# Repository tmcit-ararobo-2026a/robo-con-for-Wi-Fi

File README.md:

# < robo-con-for-Wi-Fi >

<!-- 一行でプロジェクトを説明する -->
the code and pcb in this repository is wireless robot's controller.     

## 目次

1. [概要](#1-概要)
2. [ドキュメント](#2-ドキュメント)
3. [コントリビューション](#3-コントリビューション)
4. [ビルド・使い方](#4-ビルド使い方)
5. [システム構成](#5-システム構成)
6. [ライセンス](#6-ライセンス)

## 1. 概要

<!-- プロジェクトの目的・背景・解決する課題を記述 -->
ロボコンなどの会場のなかでは2.4GHzもしくは5GHzといった周波数帯は多くの場合かなり混雑していることが多い。    
こういった大会で無線による有利は勝敗に大きく作用するため、使用する周波数はできるだけ混雑していないことが望ましい。  
そのため、6GHzを使うコントローラーを作成する。  

## 2. ドキュメント

| ドキュメント | 説明 |
| :-: | :-: |
| [CONTRIBUTING.md](./CONTRIBUTING.md) | 開発フロー・コミット規約・コーディング規約 |
| [docs/coding-rules.md](./docs/coding-rules.md) | コーディング規約の詳細 |
| [docs/uml/](./docs/uml/) | UML図 |

## 3. コントリビューション

[CONTRIBUTING.md](./CONTRIBUTING.md) を参照してください。

## 4. ビルド・使い方

<!-- ビルドのやり方 -->
<!-- 使い方 -->

## 5. システム構成

<!-- ROS2ノード構成・STM32との通信方式・ハードウェア構成 等 -->
<!-- 依存クラスが3つ以上ある場合は docs/uml/ にUML図を作成し、ここにリンクする -->

## 6. ライセンス

本リポジトリは [MITライセンス](./LICENSE) のもとで公開されています。

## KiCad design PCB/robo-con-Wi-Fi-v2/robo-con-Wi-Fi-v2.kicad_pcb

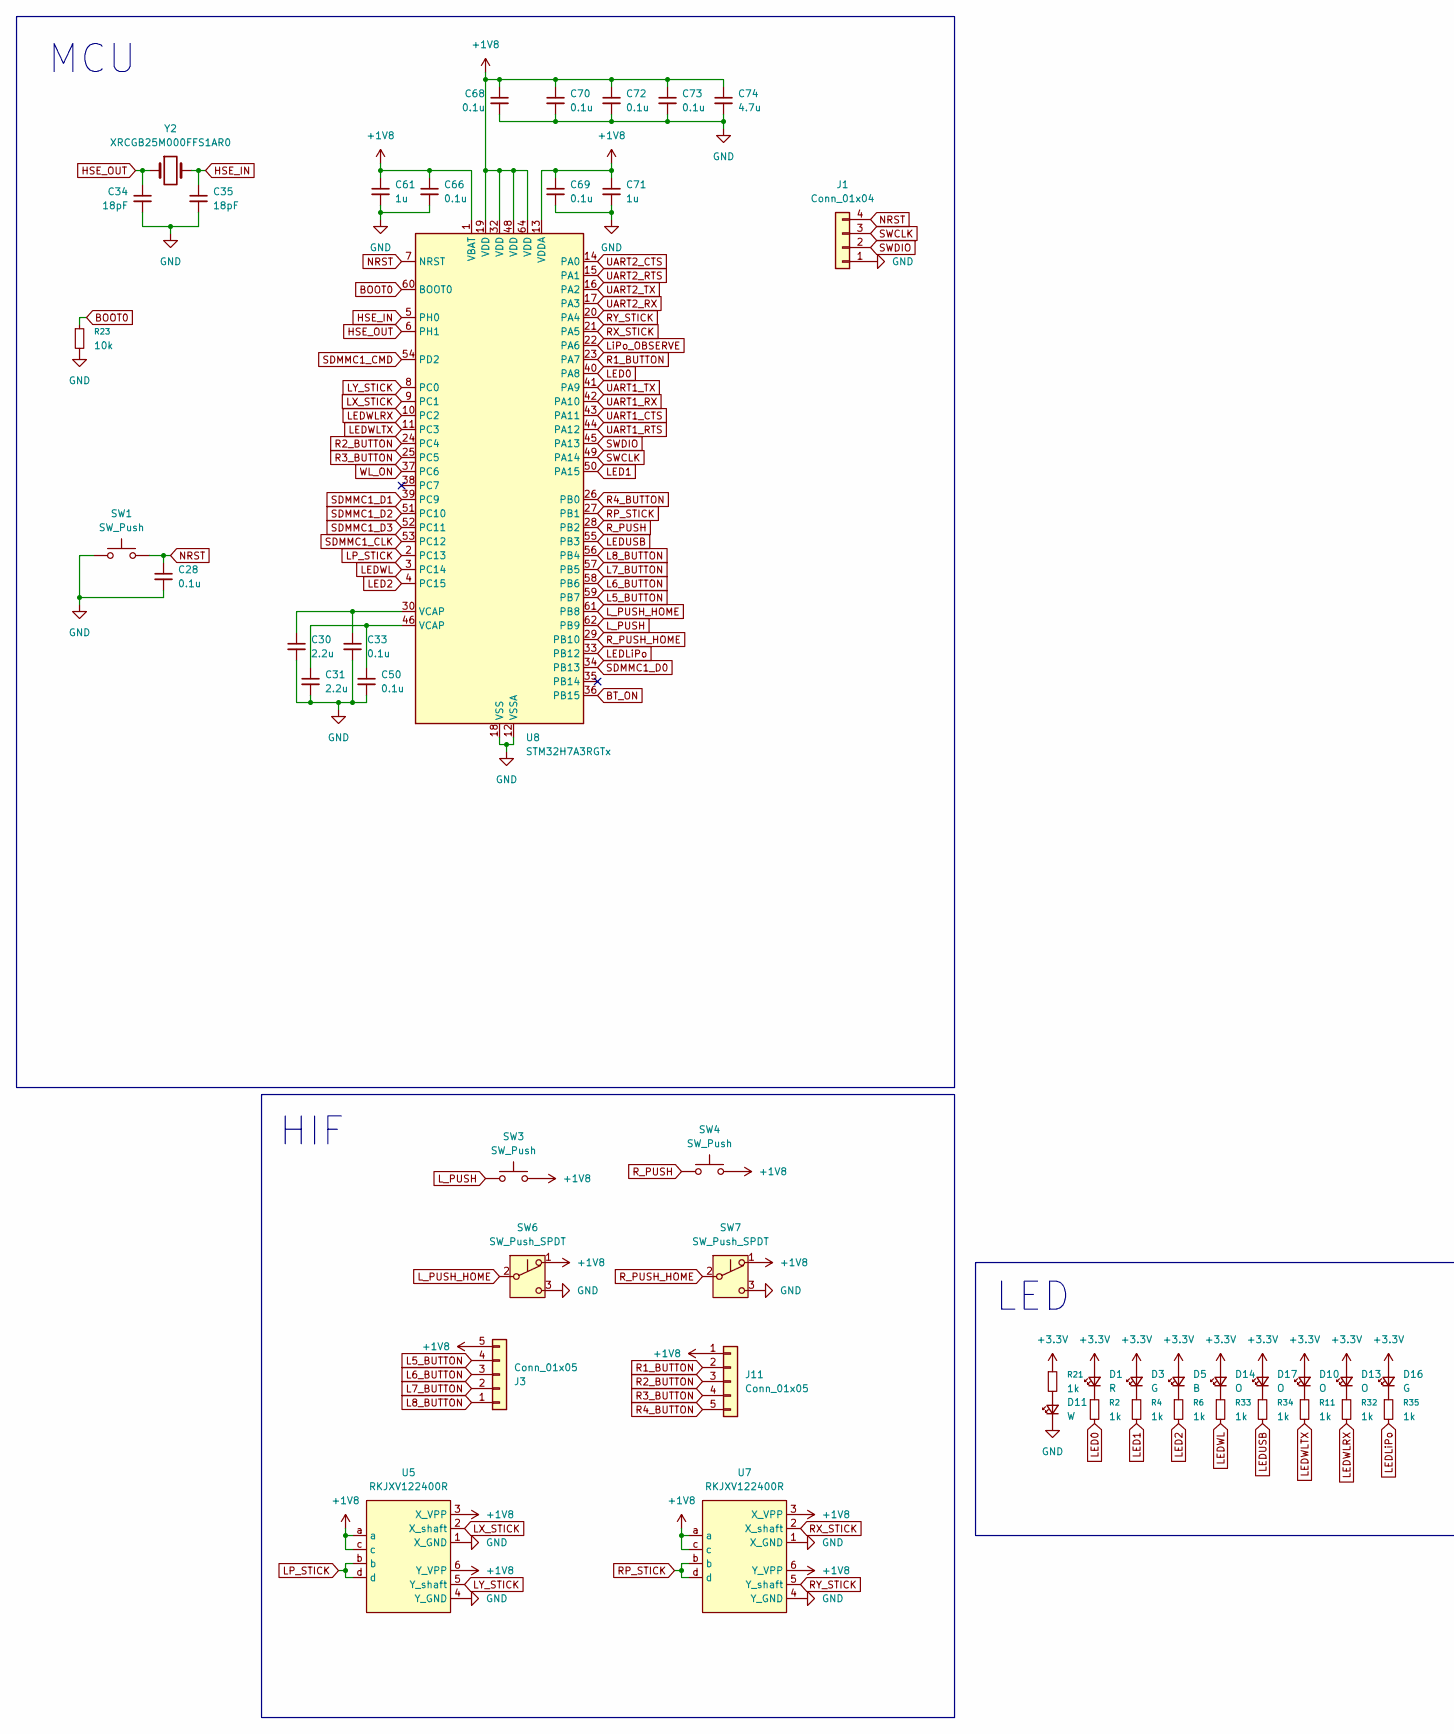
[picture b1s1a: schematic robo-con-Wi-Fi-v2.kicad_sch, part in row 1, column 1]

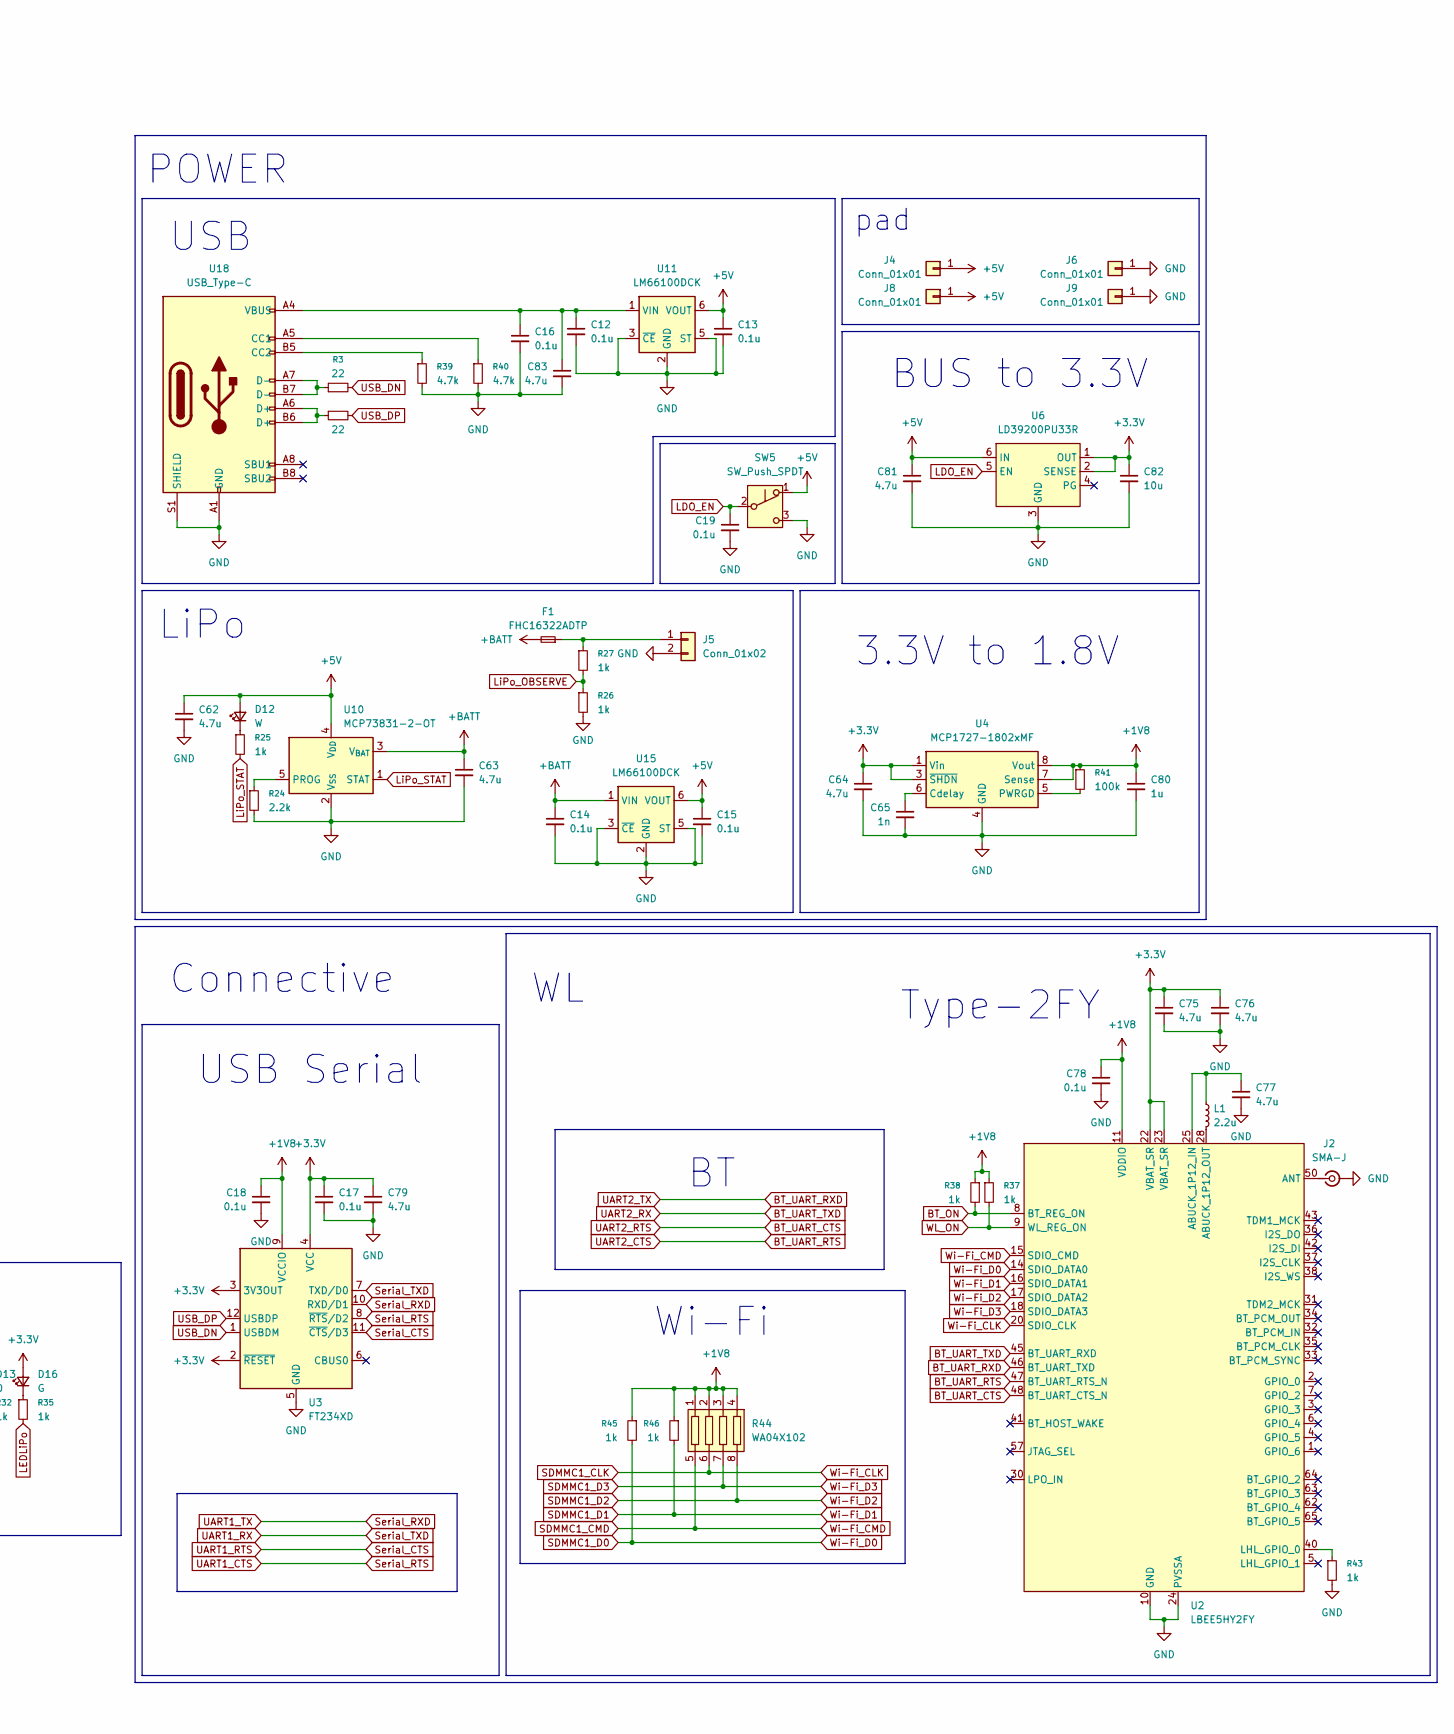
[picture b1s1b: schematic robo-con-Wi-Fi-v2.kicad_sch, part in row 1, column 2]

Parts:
C12, C13, C14, C15, C16, C17, C18, C19, C28, C33, C50, C66, C68, C69, C70, C72, C73, C78: 0.1u; C_0402_1005Metric_Pad0.74x0.62mm_HandSolder
C30, C31: 2.2u; C_0402_1005Metric_Pad0.74x0.62mm_HandSolder
C34, C35: 18pF; C_0402_1005Metric_Pad0.74x0.62mm_HandSolder
C61, C71, C80: 1u; C_0402_1005Metric_Pad0.74x0.62mm_HandSolder
C62, C63, C64, C74, C75, C76, C77, C79, C81, C83: 4.7u; C_0402_1005Metric_Pad0.74x0.62mm_HandSolder
C65: 1n; C_0402_1005Metric_Pad0.74x0.62mm_HandSolder
C82: 10u; C_0603_1608Metric_Pad1.08x0.95mm_HandSolder
D1: R; D_0603_1608Metric_Pad1.05x0.95mm_HandSolder
D3, D16: G; D_0603_1608Metric_Pad1.05x0.95mm_HandSolder
D5: B; D_0603_1608Metric_Pad1.05x0.95mm_HandSolder
D10, D13, D14, D17: O; D_0603_1608Metric_Pad1.05x0.95mm_HandSolder
D11, D12: W; D_0603_1608Metric_Pad1.05x0.95mm_HandSolder
F1: FHC16322ADTP; L_0603_1608Metric_Pad1.05x0.95mm_HandSolder
J1: Conn_01x04; PinSocket_1x04_P2.54mm_Vertical
J2: SMA-J; SMA_Conn
J3, J11: Conn_01x05; JST_ZH_B5B-ZR_1x05_P1.50mm_Vertical
J4, J6, J8, J9: Conn_01x01; SolderWirePad_1x01_SMD_1.5x3mm
J5: Conn_01x02; JST_PH_S2B-PH-K_1x02_P2.00mm_Horizontal
L1: 2.2u; L_1008_2520Metric_Pad1.43x2.20mm_HandSolder
R2, R4, R6, R11, R21, R25, R32, R33, R34, R35, R37, R38, R43, R45, R46: 1k; R_0402_1005Metric_Pad0.72x0.64mm_HandSolder
R3, R5: 22; R_0402_1005Metric_Pad0.72x0.64mm_HandSolder
R23: 10k; R_0402_1005Metric_Pad0.72x0.64mm_HandSolder
R24: 2.2k; R_0603_1608Metric_Pad0.98x0.95mm_HandSolder
R26, R27: 1k; R_0603_1608Metric_Pad0.98x0.95mm_HandSolder
R39, R40: 4.7k; R_0402_1005Metric_Pad0.72x0.64mm_HandSolder
R41: 100k; R_0603_1608Metric_Pad0.98x0.95mm_HandSolder
R44: WA04X102
SW1: SW_Push; switch_TVAF06-A020B-R
SW3, SW4: SW_Push; SKHHLPA010
SW5: SW_Push_SPDT; 4MS1R202M6QES
SW6, SW7: SW_Push_SPDT; 8MS8P1B05VS2QES-C13
U2: LBEE5HY2FY
U3: FT234XD; WDFN-12-1EP_3x3mm_P0.45mm_EP1.7x2.5mm
U4: MCP1727-1802xMF; DFN-8-1EP_3x3mm_P0.65mm_EP1.55x2.4mm
U5, U7: RKJXV122400R
U6: LD39200PU33R; DFN-6-1EP_3x3mm_P0.95mm_EP1.7x2.6mm
U8: STM32H7A3RGTx; LQFP-64_10x10mm_P0.5mm
U10: MCP73831-2-OT; SOT-23-5
U11, U15: LM66100DCK; SOT-363_SC-70-6
U18: USB_Type-C; USB_C_Receptacle_Nelton_5077CR-16-SMC2-BK-TR
Y2: XRCGB25M000FFS1AR0

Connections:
+1V8: C18.1, C61.1, C66.1, C68.1, C69.1, C70.1, C71.1, C72.1, C73.1, C74.1, C78.1, C80.1, J3.5, J11.1, R37.1, R38.1, R41.1, R44.1, R44.2, R44.3, R44.4, R45.1, R46.1, SW3.2, SW4.2, SW6.1 (A), SW7.1 (A), U2.11 (VDDIO), U3.9 (VCCIO), U4.7 (Sense), U4.8 (Vout), U5.3 (X_VPP), U5.6 (Y_VPP), U5.a, U5.c, U7.3 (X_VPP), U7.6 (Y_VPP), U7.a, U7.c, U8.1 (VBAT), U8.13 (VDDA), U8.19 (VDD), U8.32 (VDD), U8.48 (VDD), U8.64 (VDD)
+3.3V: C17.1, C64.1, C75.1, C76.1, C79.1, C82.1, D1.2 (A), D3.2 (A), D5.2 (A), D10.2 (A), D13.2 (A), D14.2 (A), D16.2 (A), D17.2 (A), R21.1, U2.22 (VBAT_SR), U2.23 (VBAT_SR), U3.2 (~RESET), U3.3 (3V3OUT), U3.4 (VCC), U4.1 (Vin), U4.2 (Vin), U4.3 (~SHDN), U6.1 (OUT), U6.2 (SENSE)
+5V: C13.1, C15.1, C62.1, C81.1, D12.2 (A), J4.1 (Pin_1_1), J8.1 (Pin_1_1), SW5.1 (A), U6.6 (IN), U10.4 (V_{DD}), U11.6 (VOUT), U15.6 (VOUT)
+BATT: C14.1, C63.1, F1.2, U10.3 (V_{BAT}), U15.1 (VIN)
BOOT0: R23.1, U8.60 (BOOT0)
BT_ON: R38.2, U2.8 (BT_REG_ON), U8.36 (PB15)
BT_UART_CTS: U2.48 (BT_UART_CTS_N), U8.15 (PA1)
BT_UART_RTS: U2.47 (BT_UART_RTS_N), U8.14 (PA0)
BT_UART_RXD: U2.46 (BT_UART_TXD), U8.16 (PA2)
BT_UART_TXD: U2.45 (BT_UART_RXD), U8.17 (PA3)
GND: C12.2, C13.2, C14.2, C15.2, C16.2, C17.2, C18.2, C19.2, C28.2, C30.2, C31.2, C33.2, C34.2, C35.2, C50.2, C61.2, C62.2, C63.2, C64.2, C65.2, C66.2, C68.2, C69.2, C70.2, C71.2, C72.2, C73.2, C74.2, C75.2, C76.2, C77.2, C78.2, C79.2, C80.2, C81.2, C82.2, C83.2, D11.1 (K), J1.1, J2.2 (Ext), J5.2, J6.1 (Pin_1_1), J9.1 (Pin_1_1), R23.2, R24.2, R26.2, R39.2, R40.2, R43.2, SW1.1, SW5.3 (C), SW6.3 (C), SW7.3 (C), U2.10 (GND), U2.12 (GND), U2.13 (GND), U2.19 (GND), U2.21 (GND), U2.24 (PVSSA), U2.26 (PVSSA), U2.27 (PVSSA), U2.29 (GND), U2.39 (GND), U2.44 (GND), U2.49 (GND), U2.51 (GND), U2.52 (GND), U2.53 (GND), U2.55 (GND), U2.56 (GND), U2.58 (GND), U2.59 (GND), U2.60 (GND), U2.61 (GND), U2.66 (GND), U2.67 (GND), U2.68 (GND), U2.69 (GND), U2.70 (GND), U2.71 (GND), U2.72 (GND), U3.5 (GND), U3.13 (GND), U4.4 (GND), U4.9 (GND), U5.1 (X_GND), U5.4 (Y_GND), U6.3 (GND), U6.7 (GND), U7.1 (X_GND), U7.4 (Y_GND), U8.12 (VSSA), U8.18 (VSS), U8.31 (VSS), U8.47 (VSS), U8.63 (VSS), U10.2 (V_{SS}), U11.2 (GND), U11.3 (~CE), U11.5 (ST), U15.2 (GND), U15.3 (~CE), U15.5 (ST), U18.A1 (GND), U18.B1 (GND), U18.S1 (SHIELD)
HSE_IN: C35.1, U8.5 (PH0), Y2.3 (2)
HSE_OUT: C34.1, U8.6 (PH1), Y2.1
L5_BUTTON: J3.4, U8.59 (PB7)
L6_BUTTON: J3.3, U8.58 (PB6)
L7_BUTTON: J3.2, U8.57 (PB5)
L8_BUTTON: J3.1, U8.56 (PB4)
LDO_EN: C19.1, SW5.2 (B), U6.5 (EN)
LED0: R2.2, U8.40 (PA8)
LED1: R4.2, U8.50 (PA15)
LED2: R6.2, U8.4 (PC15)
LEDLiPo: R35.2, U8.33 (PB12)
LEDUSB: R34.2, U8.55 (PB3)
LEDWL: R33.2, U8.3 (PC14)
LEDWLRX: R32.2, U8.10 (PC2)
LEDWLTX: R11.2, U8.11 (PC3)
LP_STICK: U5.b, U5.d, U8.2 (PC13)
LX_STICK: U5.2 (X_shaft), U8.9 (PC1)
LY_STICK: U5.5 (Y_shaft), U8.8 (PC0)
L_PUSH: SW3.1, U8.62 (PB9)
L_PUSH_HOME: SW6.2 (B), U8.61 (PB8)
LiPo_OBSERVE: R26.1, R27.2, U8.22 (PA6)
LiPo_STAT: R25.2, U10.1 (STAT)
NRST: C28.1, J1.4, SW1.2, U8.7 (NRST)
unnamed: C30.1, C33.1, U8.30 (VCAP)
unnamed: C31.1, C50.1, U8.46 (VCAP)
unnamed: D1.1 (K), R2.1
unnamed: D3.1 (K), R4.1
unnamed: D5.1 (K), R6.1
unnamed: D10.1 (K), R11.1
unnamed: D11.2 (A), R21.2
unnamed: D12.1 (K), R25.1
unnamed: D13.1 (K), R32.1
unnamed: D14.1 (K), R33.1
unnamed: D16.1 (K), R35.1
unnamed: D17.1 (K), R34.1
unnamed: J2.1 (In), U2.50 (ANT)
unnamed: F1.1, J5.1, R27.1
unnamed: R3.1, U18.A7 (D-), U18.B7 (D-)
unnamed: R5.1, U18.A6 (D+), U18.B6 (D+)
unnamed: C77.1, L1.1, U2.25 (ABUCK_1P12_IN)
unnamed: L1.2, U2.28 (ABUCK_1P12_OUT)
unnamed: R43.1, U2.40 (LHL_GPIO_0)
unnamed: C65.1, U4.6 (Cdelay)
unnamed: R41.2, U4.5 (PWRGD)
unnamed: R24.1, U10.5 (PROG)
unnamed: C12.1, C16.1, C83.1, U11.1 (VIN), U18.A4 (VBUS), U18.B4 (VBUS)
unnamed: R40.1, U18.A5 (CC1)
unnamed: R39.1, U18.B5 (CC2)
R1_BUTTON: J11.2, U8.23 (PA7)
R2_BUTTON: J11.3, U8.24 (PC4)
R3_BUTTON: J11.4, U8.25 (PC5)
R4_BUTTON: J11.5, U8.26 (PB0)
RP_STICK: U7.b, U7.d, U8.27 (PB1)
RX_STICK: U7.2 (X_shaft), U8.21 (PA5)
RY_STICK: U7.5 (Y_shaft), U8.20 (PA4)
R_PUSH: SW4.1, U8.28 (PB2)
R_PUSH_HOME: SW7.2 (B), U8.29 (PB10)
SDMMC1_CLK: R44.6, U2.20 (SDIO_CLK), U8.53 (PC12)
SDMMC1_CMD: R44.5, U2.15 (SDIO_CMD), U8.54 (PD2)
SDMMC1_D0: R45.2, U2.14 (SDIO_DATA0), U8.34 (PB13)
SDMMC1_D1: R46.2, U2.16 (SDIO_DATA1), U8.39 (PC9)
SDMMC1_D2: R44.8, U2.17 (SDIO_DATA2), U8.51 (PC10)
SDMMC1_D3: R44.7, U2.18 (SDIO_DATA3), U8.52 (PC11)
SWCLK: J1.3, U8.49 (PA14)
SWDIO: J1.2, U8.45 (PA13)
Serial_CTS: U3.11 (~CTS/D3), U8.44 (PA12)
Serial_RTS: U3.8 (~RTS/D2), U8.43 (PA11)
Serial_RXD: U3.10 (RXD/D1), U8.41 (PA9)
Serial_TXD: U3.7 (TXD/D0), U8.42 (PA10)
USB_DN: R3.2, U3.1 (USBDM)
USB_DP: R5.2, U3.12 (USBDP)
WL_ON: R37.2, U2.9 (WL_REG_ON), U8.37 (PC6)

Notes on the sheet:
Connective
pad
Type-2FY
USB Serial
USB
LiPo
BUS to 3.3V
Wi-Fi
POWER
LED
3.3V to 1.8V
MCU
HIF

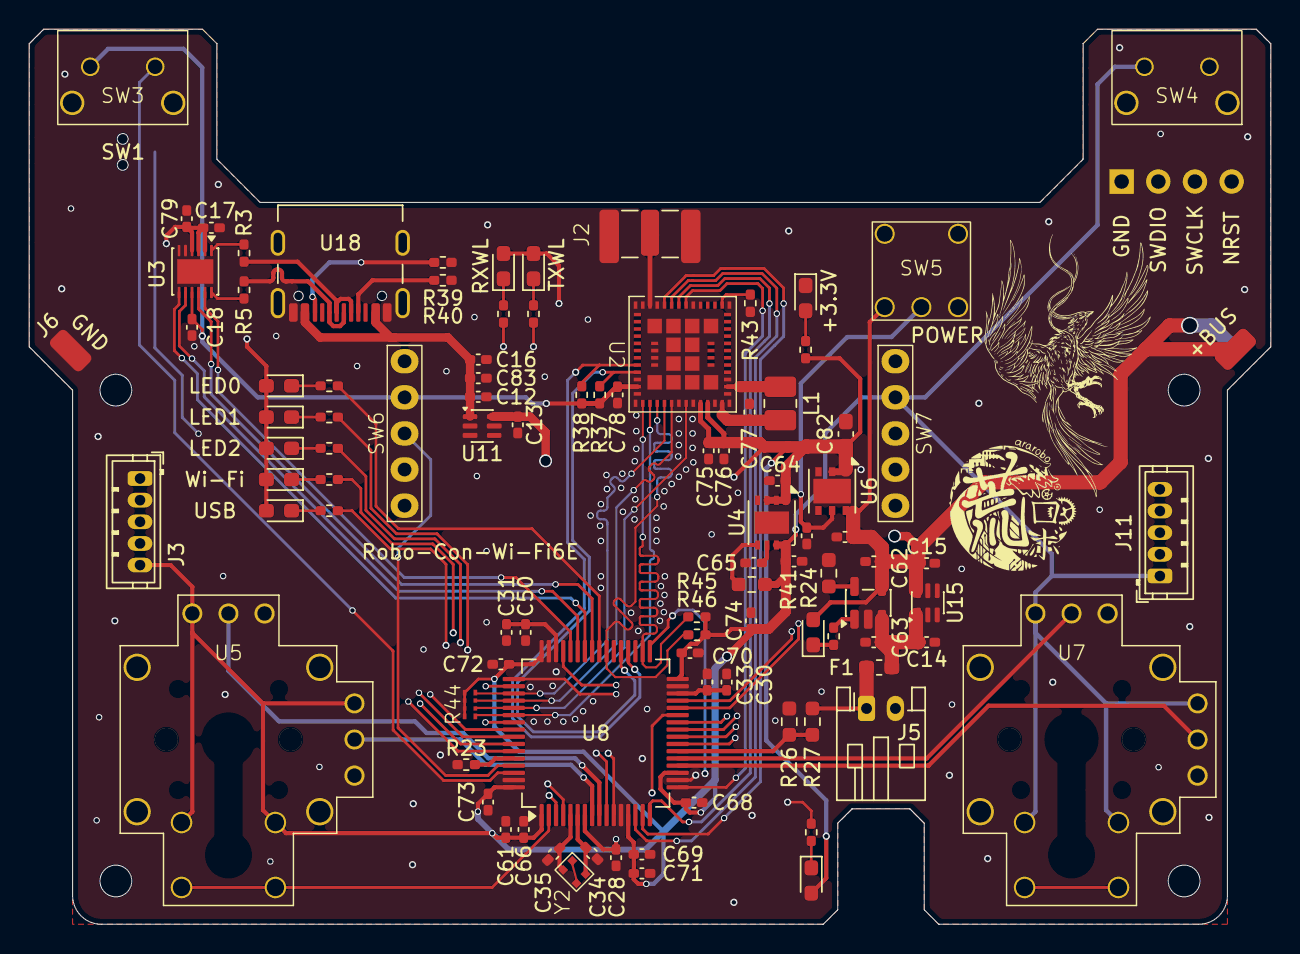
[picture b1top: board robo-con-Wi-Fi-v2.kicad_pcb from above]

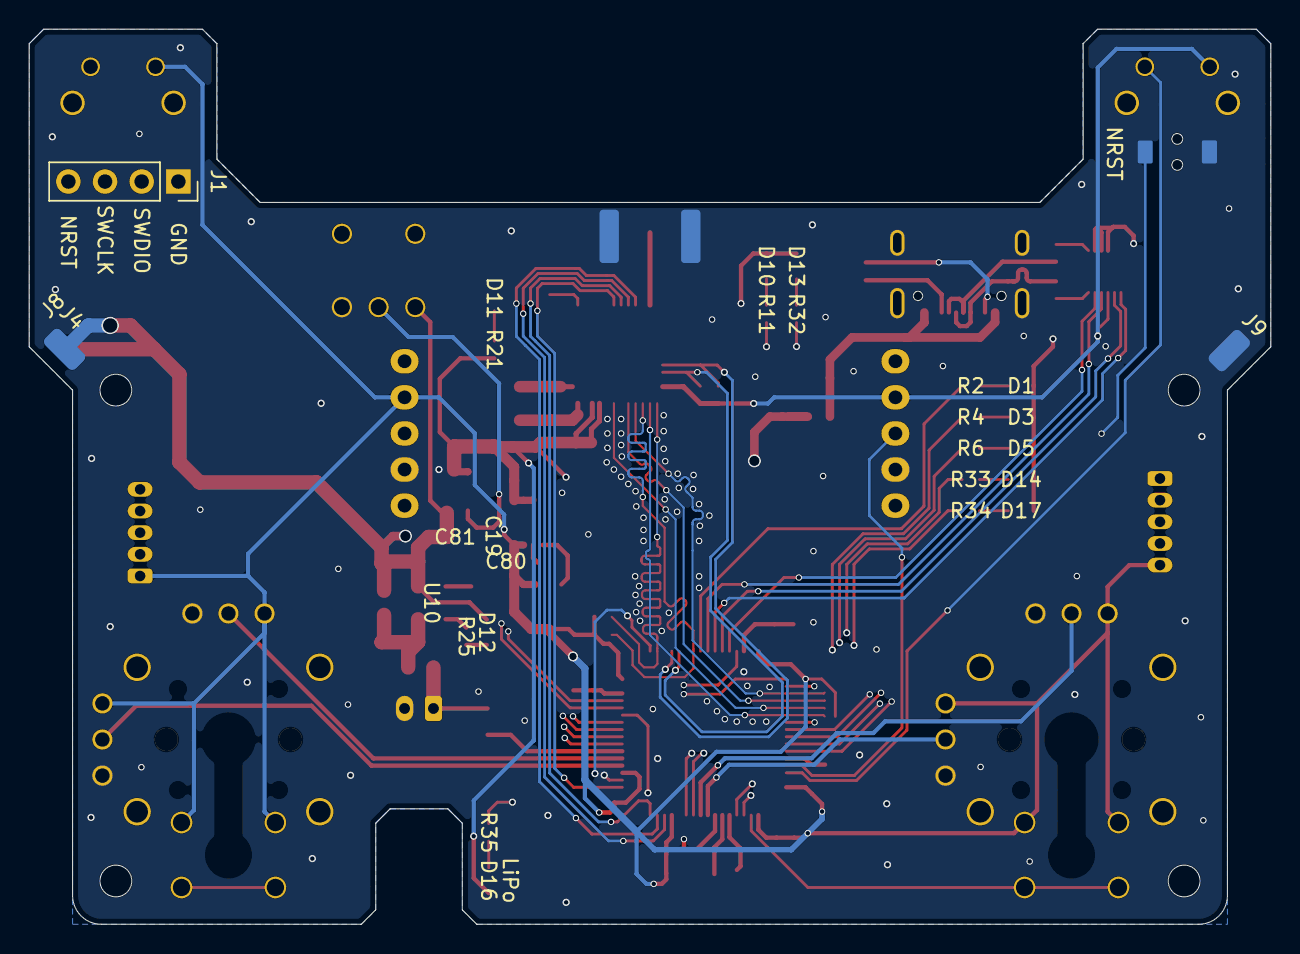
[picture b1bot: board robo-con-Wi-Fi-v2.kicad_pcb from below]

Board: 4 copper layers, 86.0 x 62.0 mm, 101 parts (4 on the bottom side), 83 nets.

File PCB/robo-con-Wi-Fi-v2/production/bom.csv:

Designator,Footprint,Quantity,Value,LCSC Part #
"C12, C13, C14, C15, C16, C17, C18, C19, C28, C33, C50, C66, C68, C69, C70, C72, C73, C78",0402,18,0.1u,
"C30, C31",0402,2,2.2u,
"C34, C35",0402,2,18pF,
"C61, C71, C80",0402,3,1u,
"C62, C63, C64, C74, C75, C76, C77, C79, C81, C83",0402,10,4.7u,
C65,0402,1,1n,
C82,0603,1,10u,
D1,0603,1,R,
"D10, D13, D14, D17",0603,4,O,
"D11, D12",0603,2,W,
"D16, D3",0603,2,G,
D5,0603,1,B,
F1,0603,1,FHC16322ADTP,
J1,PinSocket_1x04_P2.54mm_Vertical,1,Conn_01x04,
"J11, J3",JST_ZH_B5B-ZR_1x05_P1.50mm_Vertical,2,Conn_01x05,
J2,SMA_Conn,1,SMA-J,
"J4, J6, J8, J9",SolderWirePad_1x01_SMD_1.5x3mm,4,Conn_01x01,
J5,JST_PH_S2B-PH-K_1x02_P2.00mm_Horizontal,1,Conn_01x02,
L1,1008,1,2.2u,
"R11, R2, R21, R25, R32, R33, R34, R35, R37, R38, R4, R43, R45, R46, R6",0402,15,1k,
R23,0402,1,10k,
R24,0603,1,2.2k,
"R26, R27",0603,2,1k,
"R3, R5",0402,2,22,
"R39, R40",0402,2,4.7k,
R41,0603,1,100k,
R44,WA04X102,1,WA04X102,
SW1,switch_TVAF06-A020B-R,1,SW_Push,
"SW3, SW4",SKHHLPA010,2,SW_Push,
SW5,4MS1R202M6QES,1,SW_Push_SPDT,
"SW6, SW7",8MS8P1B05VS2QES-C13,2,SW_Push_SPDT,
U10,SOT-23-5,1,MCP73831-2-OT,
"U11, U15",SOT-363_SC-70-6,2,LM66100DCK,
U18,USB_C_Receptacle_Nelton_5077CR-16-SMC2-BK-TR,1,USB_Type-C,
U2,LBEE5HY2FY,1,LBEE5HY2FY,
U3,WDFN-12-1EP_3x3mm_P0.45mm_EP1.7x2.5mm,1,FT234XD,
U4,DFN-8-1EP_3x3mm_P0.65mm_EP1.55x2.4mm,1,MCP1727-1802xMF,
"U5, U7",RKJXV122400R,2,RKJXV122400R,
U6,DFN-6-1EP_3x3mm_P0.95mm_EP1.7x2.6mm,1,LD39200PU33R,
U8,LQFP-64_10x10mm_P0.5mm,1,STM32H7A3RGTx,
Y2,XRCGB25M000FFS1AR0,1,XRCGB25M000FFS1AR0,
